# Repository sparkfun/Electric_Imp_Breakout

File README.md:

Electric Imp Breakout
=====================

[
*Electric Imp Breakout (BOB-12886)*](https://www.sparkfun.com/products/12886)

The Electric Imp Breakout Board allows you to explore the capabilities of the Imp by providing standard 0.1" headers to solder
as well as the necessary CryptAuthEE IC to identify your prototype to the Imp Cloud service. 

Repository Contents
-------------------
* **/Hardware** - All Eagle design files (.brd, .sch)
* **/Production** - Test bed files and production panel files

Product Versions
----------------
* [BOB-11400](https://www.sparkfun.com/products/11400)- Version 1.1 for sale on SparkFun. 

Version History
---------------
* [v1.1](https://github.com/sparkfun/Electric_Imp_Breakout/tree/V_1.1) Version 1.1 of the Imp Breakout, with the old SD socket footprint.

License Information
-------------------
The hardware is released under [Creative Commons ShareAlike 4.0 International](https://creativecommons.org/licenses/by-sa/4.0/).

Distributed as-is; no warranty is given.

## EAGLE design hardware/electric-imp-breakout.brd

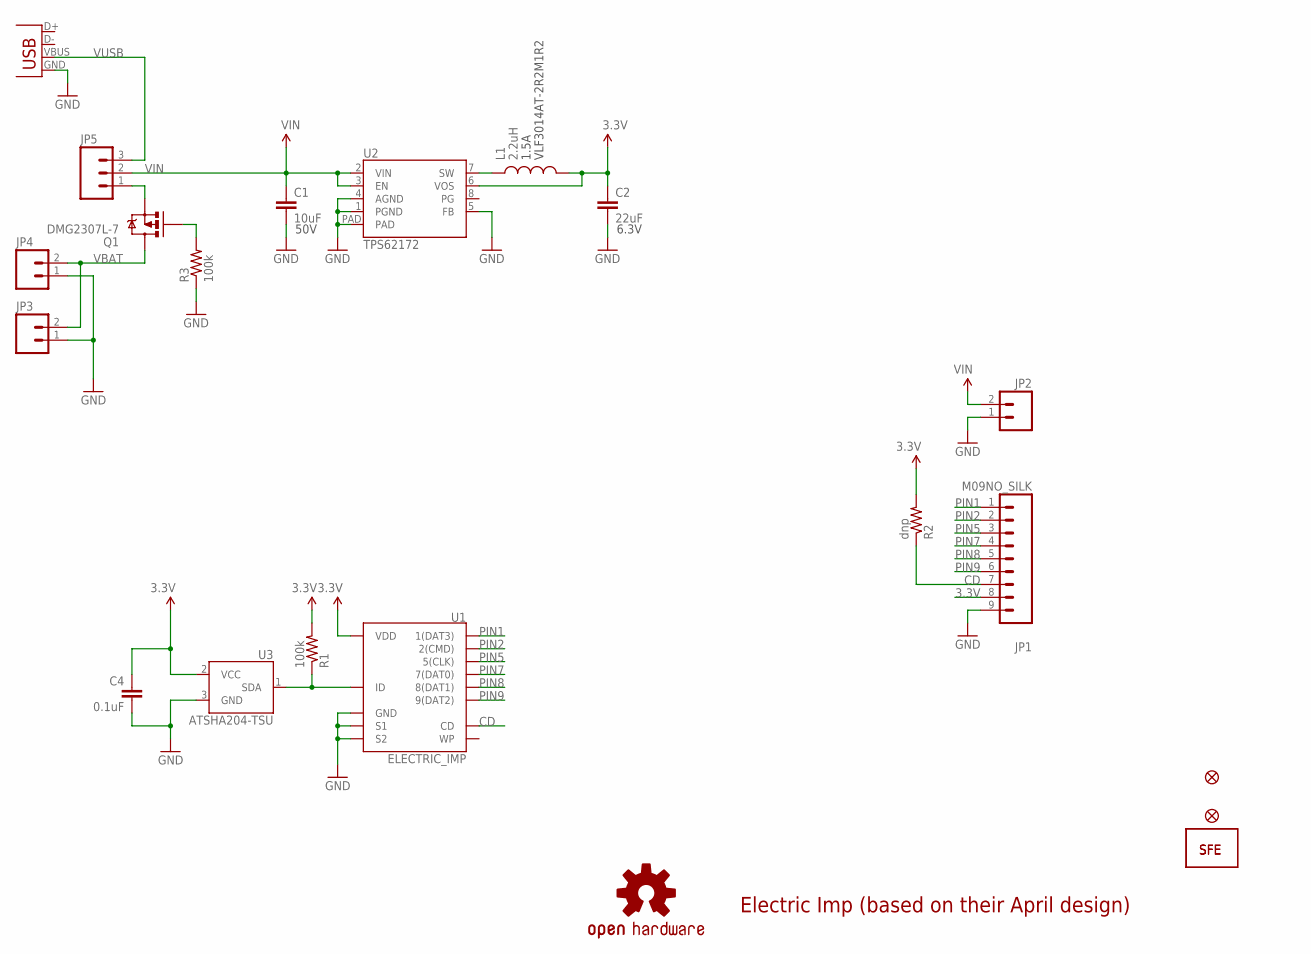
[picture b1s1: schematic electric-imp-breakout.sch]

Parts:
C1: 10uF; 1210
C2: 22uF; 0805
C4: 0.1uF; 0402-CAP
FID1, FID2: FIDUCIAL1X2; FIDUCIAL-1X2
JP1: M09NO_SILK; 1X09_NO_SILK
JP2: M021X02_NO_SILK; 1X02_NO_SILK
JP3: M02SMD; 1X02_SMD
JP4: M02-JST-2-PTH-NO_SILK; JST-2-PTH-NS
JP5: M031X03_NO_SILK; 1X03_NO_SILK
JP6: LOGO-SFESK; SFE-LOGO-FLAME
JP7: LOGO-SFENEW; SFE-NEW-WEBLOGO
L1: 2.2uH; VLF4012A
Q1: DMG2307L-7; SOT23-3
R1, R3: 100k; 0402-RES
R2: dnp; 0402-RES
U1: ELECTRIC_IMP; SD_MMC_SOCKET
U2: TPS62172; WSON-8-PAD
U3: ATSHA204-TSU; SOT23-3
U$5: OSHW-LOGOS; OSHW-LOGO-S
X1: USBSMD; USB-MINIB

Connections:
3.3V: C2.1, C4.1, JP1.8, L1.P$2 (2), R1.2, R2.2, U1.4 (VDD), U2.6 (VOS), U3.2 (VCC); also elsewhere on the board
CD: JP1.7, R2.1, U1.CD; also elsewhere on the board
GND: C1.2, C2.2, C4.2, JP1.9, JP2.1, JP3.1, JP4.1, R3.1, U1.3 (GND), U1.S1, U1.S2, U2.1 (PGND), U2.4 (AGND), U2.5 (FB), U2.PAD, U3.3 (GND), X1.GND; also elsewhere on the board
ID: R1.1, U1.6 (ID), U3.1 (SDA); also elsewhere on the board
unnamed: L1.P$1 (1), U2.7 (SW)
unnamed: Q1.1 (G), R3.2
unnamed: JP5.1, Q1.2 (S)
PIN1: JP1.1, U1.1 (1(DAT3)); also elsewhere on the board
PIN2: JP1.2, U1.2 (2(CMD)); also elsewhere on the board
PIN5: JP1.3, U1.5 (5(CLK)); also elsewhere on the board
PIN7: JP1.4, U1.7 (7(DAT0)); also elsewhere on the board
PIN8: JP1.5, U1.8 (8(DAT1)); also elsewhere on the board
PIN9: JP1.6, U1.9 (9(DAT2)); also elsewhere on the board
VBAT: JP3.2, JP4.2, Q1.3 (D)
VIN: C1.1, JP2.2, JP5.2, U2.2 (VIN), U2.3 (EN)
VUSB: JP5.3, X1.VBUS

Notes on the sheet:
50V
6.3V
1.5A
VLF3014AT-2R2M1R2
Electric Imp (based on their April design)

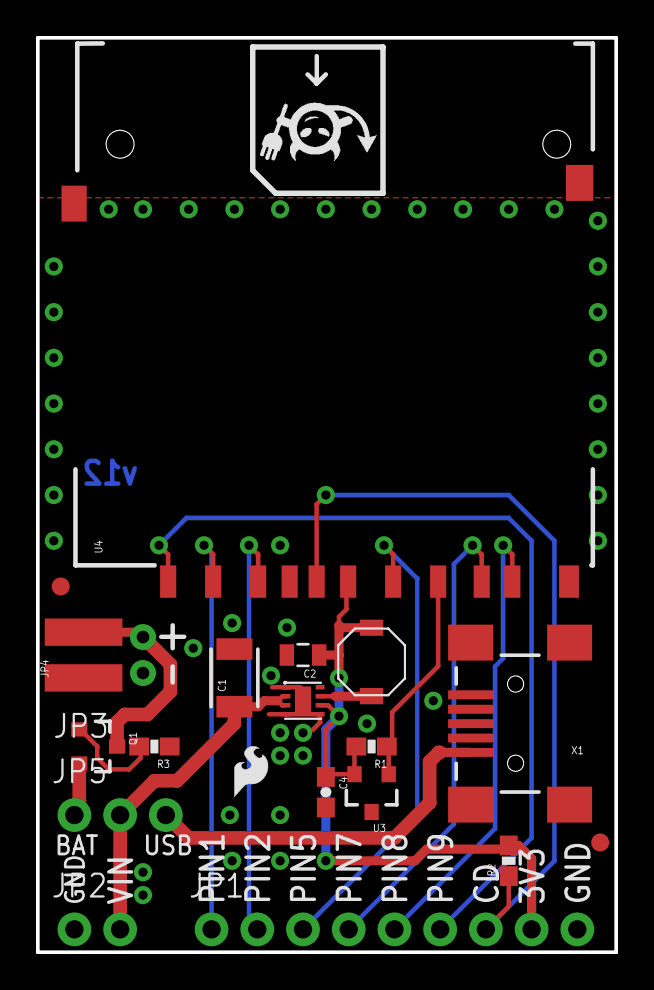
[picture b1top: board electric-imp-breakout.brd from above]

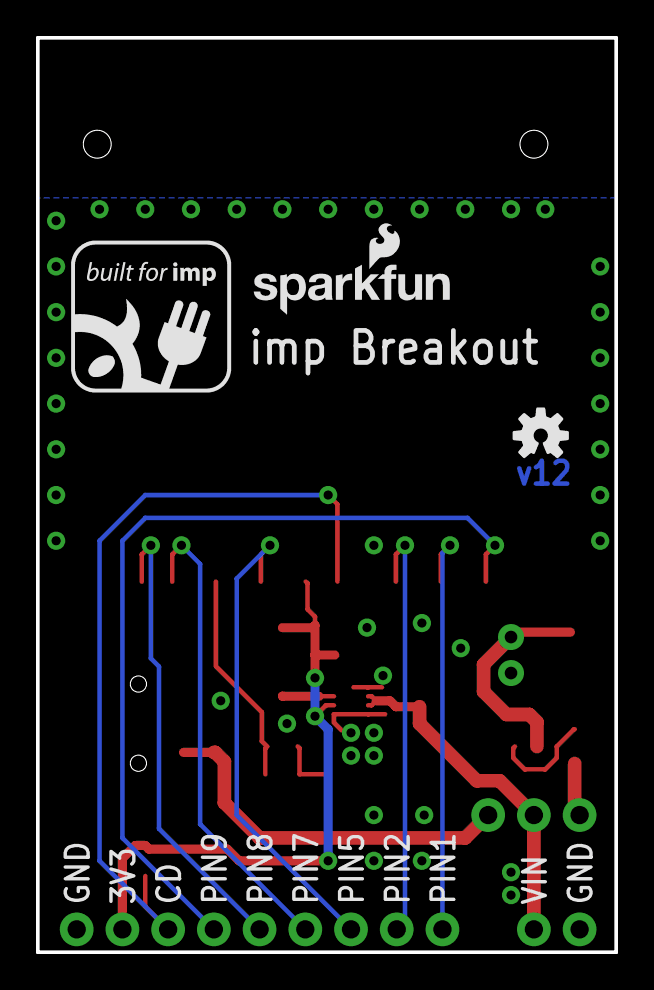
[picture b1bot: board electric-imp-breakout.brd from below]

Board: 2 copper layers, 32.1 x 50.8 mm, 24 parts (2 on the bottom side), 16 nets.

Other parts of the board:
FRAME1: FRAME-LETTER; CREATIVE_COMMONS
U4: ELECTRIC_IMP; SD_1:1
U$3: REVISION

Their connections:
3.3V: U4.4; also elsewhere on the board
CD: U4.CD; also elsewhere on the board
GND: U4.3, U4.SH@1, U4.SH@2; also elsewhere on the board
ID: U4.6; also elsewhere on the board
PIN1: U4.1; also elsewhere on the board
PIN2: U4.2; also elsewhere on the board
PIN5: U4.5; also elsewhere on the board
PIN7: U4.7; also elsewhere on the board
PIN8: U4.8; also elsewhere on the board
PIN9: U4.9; also elsewhere on the board

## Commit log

2014-03-07 Initial Commit with brd/sch
2014-07-03 Adding consistent board files, readme
2014-07-03 Changing to new socket FP, 0603 components, schematic updates
2014-07-07 Fixing DNP resistor to 0603, changing sparkfun logo
2014-08-07 changed micro fid to regular
2014-08-07 created panel v11
2014-08-07 created giant panel
2014-08-22 removed micro fids, added regular
2014-08-22 created v12 panels
2014-10-28 Updating README with new product info

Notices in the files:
parts and their libraries:
SparkFun-Passives: Licensing: CC v3.0 Share-Alike You are welcome to use this library for commercial purposes.
SparkFun-Resistors: Licensing: Creative Commons ShareAlike 4.0 International - https://creativecommons.org/licenses/by-sa/4.0
SparkFun-Aesthetics: Released under the Creative Commons
